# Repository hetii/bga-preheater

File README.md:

# BGA REWORK STATION
Advanced Open-Source BGA Preheater Controller with Web Interface, Multi-Zone Heating, and Thermal Profile Management.

---

## 📖 Overview

**BGA Rework Station** is a fully open-source project designed for controlling professional and DIY BGA/PCB preheating systems.

The controller supports multiple heating zones, thermocouple monitoring, fan control, and a modern web-based interface for managing the entire process directly from a browser.

The project is suitable for:
- BGA rework stations
- PCB preheaters
- SMT/reflow experiments
- Electronics repair workshops
- DIY thermal control systems

---

# ✨ Features

## 🔥 Multi-Zone Heater Control
- Control up to **5 independent heaters**
- Separate heating zones
- Real-time power management
- Suitable for IR heaters, ceramic heaters, hotplates, and custom heating systems

## 🌡️ Thermocouple Monitoring
- Support for **6 thermocouples** and ds18b20 sensors over 1 wire
- Real-time temperature acquisition
- Multi-point PCB temperature tracking
- Accurate thermal feedback for safe BGA processing

## 🌀 Fan Control
- PWM fan control support
- Automatic or manual cooling operation
- Active thermal stabilization

## 🌐 Web Interface
Built-in web application accessible from any browser.

Features include:
- Real-time temperature monitoring
- Heater control
- Fan management
- Profile editor
- System status monitoring
- Live thermal charts

## 💾 BGA Profile Management
- Save and load BGA heating profiles
- Custom temperature curves
- Repeatable rework processes
- Profile storage directly in the system

---

# 🛠️ Hardware Capabilities

| Feature | Specification |
|---|---|
| Heater Outputs | Up to 5 |
| Thermocouple Inputs | 6 |
| Fan Control | 2 x PWM Supported |
| Interface | Web Browser |
| Profile Storage | Supported |
| Open Source | Yes |

---

# 📂 Project Structure

```text
/
├── hardware
│   ├── grb
│   ├── img
│   ├── kicad
│   └── pdf
├── README.md
└── software
    ├── builder
    ├── builder.py
    ├── configs
    ├── html
    ├── include
    ├── requirements.txt
    └── src
```

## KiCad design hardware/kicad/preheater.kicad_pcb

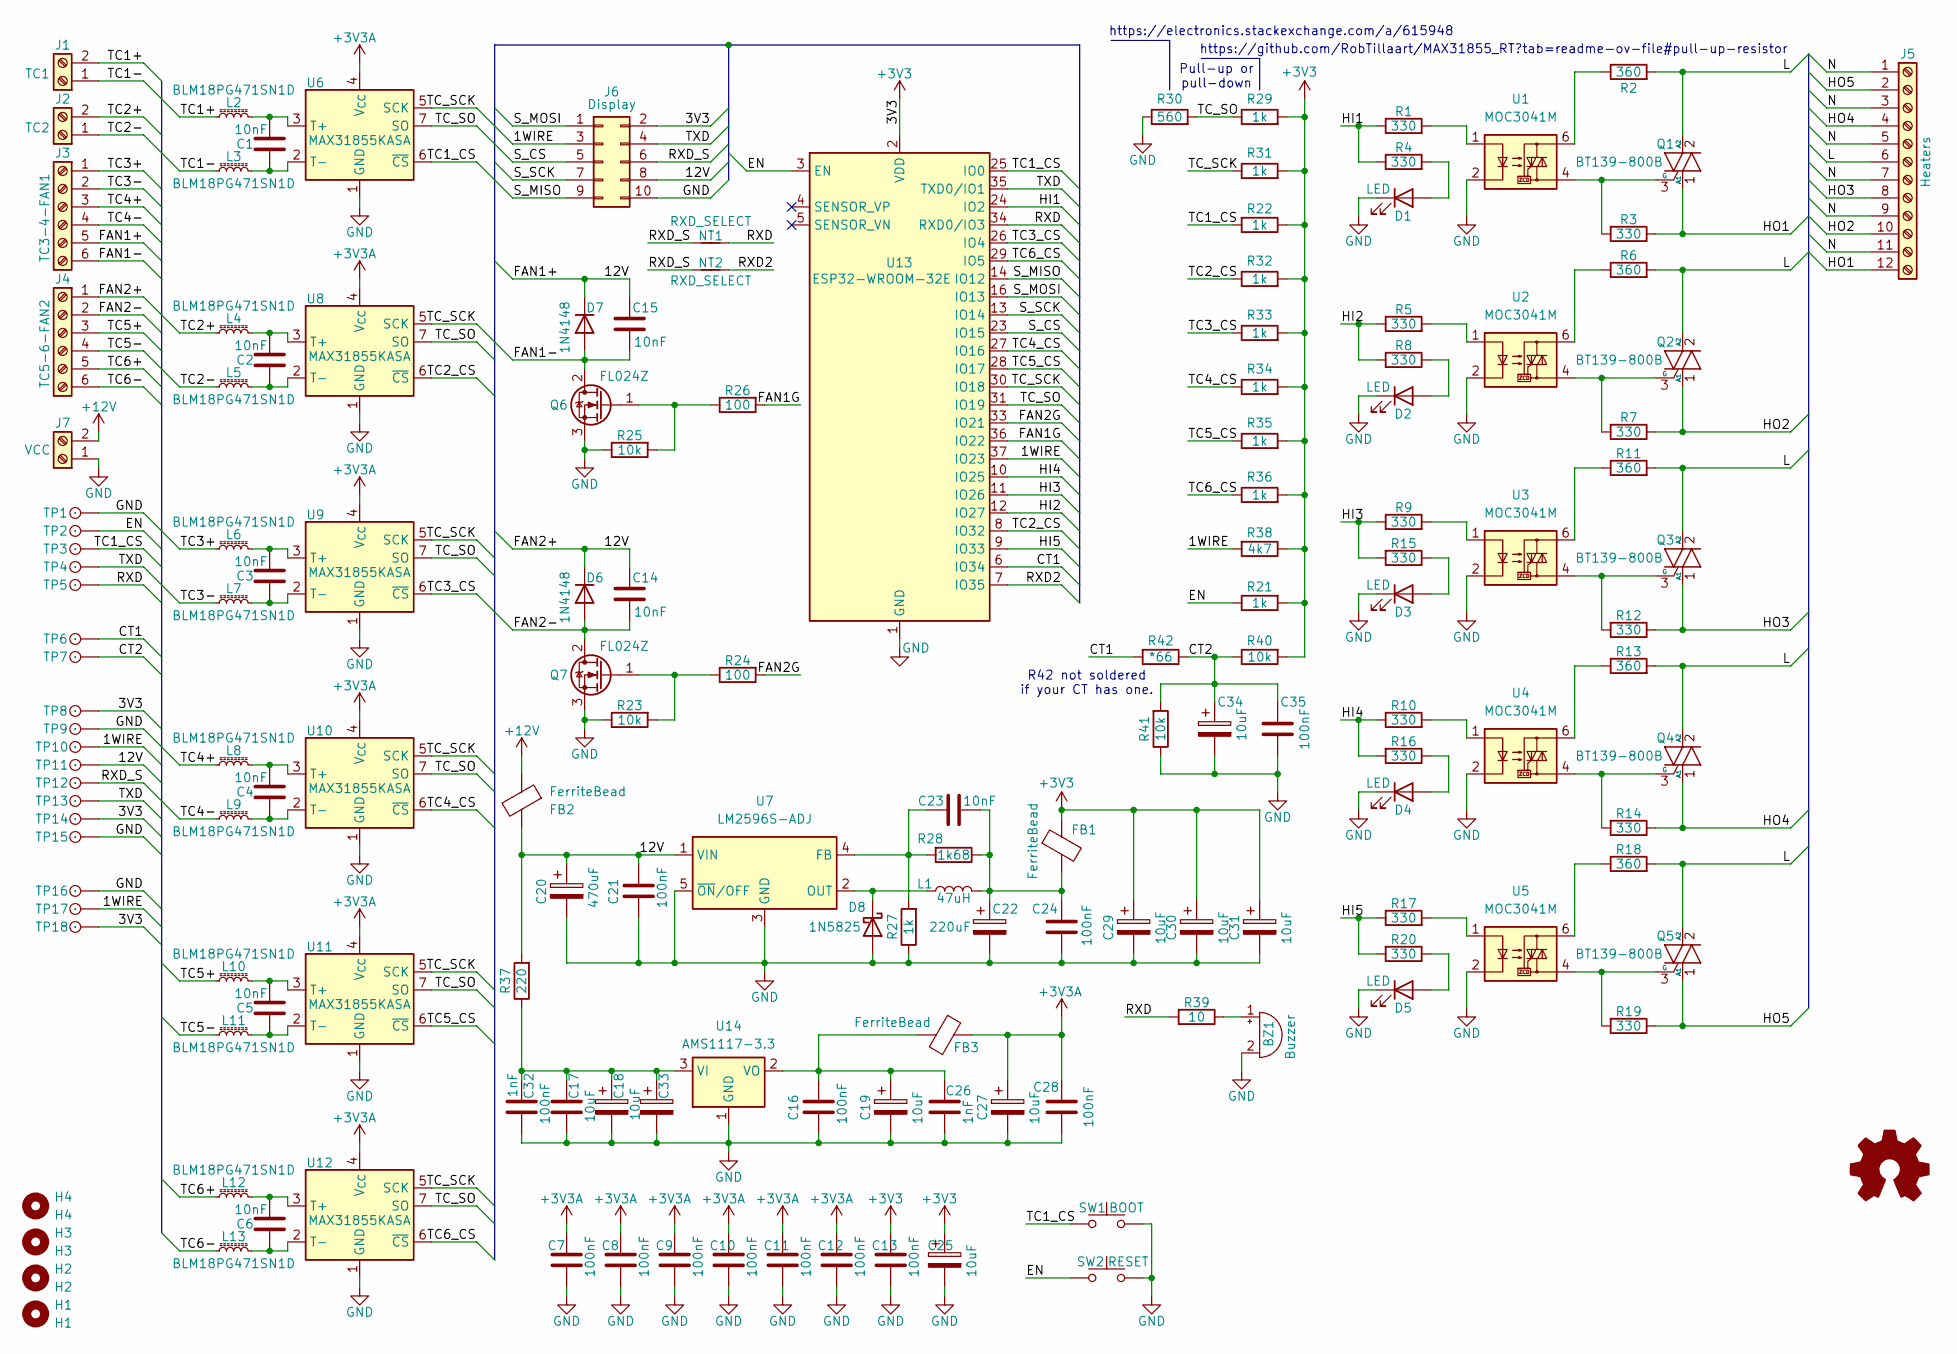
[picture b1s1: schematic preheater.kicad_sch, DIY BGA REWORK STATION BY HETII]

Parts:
BZ1: Buzzer; Buzzer_12x9.5RM7.6
C1, C2, C3, C4, C5, C6, C14, C15, C23: 10nF; C_1206_3216Metric_Pad1.33x1.80mm_HandSolder
C7, C8, C9, C10, C11, C12, C13, C16, C17, C21, C24, C28, C35: 100nF; C_1206_3216Metric_Pad1.33x1.80mm_HandSolder
C18, C19, C25, C27, C29, C30, C31, C33, C34: 10uF; C_1206_3216Metric_Pad1.33x1.80mm_HandSolder
C20: 470uF; CP_Radial_D8.0mm_P3.50mm
C22: 220uF; CP_Radial_D8.0mm_P3.50mm
C26, C32: 1nF; C_1206_3216Metric_Pad1.33x1.80mm_HandSolder
D1, D2, D3, D4, D5: LED; LED_1206_3216Metric_Pad1.42x1.75mm_HandSolder
D6, D7: 1N4148; D_MicroMELF_Handsoldering
D8: 1N5825; D_MicroMELF_Handsoldering
FB1, FB2: FerriteBead; L_Axial_L7.0mm_D3.3mm_P10.16mm_Horizontal_Fastron_MICC
FB3: FerriteBead; L_Axial_L7.0mm_D3.3mm_P2.54mm_Vertical_Fastron_MICC
H1: H1; MountingHole_3.2mm_M3_Pad_Via
H2: H2; MountingHole_3.2mm_M3_Pad_Via
H3: H3; MountingHole_3.2mm_M3_Pad_Via
H4: H4; MountingHole_3.2mm_M3_Pad_Via
J1: TC1; Altech_AK100_1x02_P5.00mm
J2: TC2; Altech_AK100_1x02_P5.00mm
J3: TC3-4-FAN1; Altech_AK100_1x06_P5.00mm
J4: TC5-6-FAN2; Altech_AK100_1x06_P5.00mm
J5: Heaters; Altech_AK300_1x12_P5.00mm_45-Degree
J6: Display; PinHeader_2x05_P2.54mm_Vertical
J7: VCC; Altech_AK100_1x02_P5.00mm
L1: 47uH; L_Bourns_SRR1260
L2, L3, L4, L5, L6, L8, L9, L10, L11, L12, L13: BLM18PG471SN1D; L_0603_1608Metric_Pad1.05x0.95mm_HandSolder
L7: BLM18PG471SN1D; R_0603_1608Metric_Pad0.98x0.95mm_HandSolder
NT1, NT2: RXD_SELECT; R_0201_0603Metric
Q1, Q2, Q3, Q4, Q5: BT139-800B; TO-220-3_Vertical
Q6, Q7: FL024Z; SOT-223-3_TabPin2
R1, R4, R5, R8, R9, R10, R15, R16, R17, R20: 330; R_1206_3216Metric_Pad1.30x1.75mm_HandSolder
R2, R6, R11, R13, R18: 360; R_1206_3216Metric_Pad1.30x1.75mm_HandSolder
R3, R7, R12, R14, R19: 330; R_Axial_DIN0204_L3.6mm_D1.6mm_P7.62mm_Horizontal
R21, R22, R27, R29, R31, R32, R33, R34, R35, R36: 1k; R_1206_3216Metric_Pad1.30x1.75mm_HandSolder
R23, R25, R40, R41: 10k; R_1206_3216Metric_Pad1.30x1.75mm_HandSolder
R24, R26: 100; R_1206_3216Metric_Pad1.30x1.75mm_HandSolder
R28: 1k68; R_1206_3216Metric_Pad1.30x1.75mm_HandSolder
R30: 560; R_1206_3216Metric_Pad1.30x1.75mm_HandSolder
R37: 220; R_1206_3216Metric_Pad1.30x1.75mm_HandSolder
R38: 4k7; R_1206_3216Metric_Pad1.30x1.75mm_HandSolder
R39: 10; R_1206_3216Metric_Pad1.30x1.75mm_HandSolder
R42: *66; R_1206_3216Metric_Pad1.30x1.75mm_HandSolder
SW1: BOOT; SW_SPST_PTS645Sx43SMTR92
SW2: RESET; SW_SPST_PTS645Sx43SMTR92
TP1, TP2, TP3, TP4, TP5, TP6, TP7, TP8, TP9, TP10, TP11, TP12, TP13, TP14, TP15, TP16, TP17, TP18: .; TestPoint_Pad_D1.5mm
U1, U2, U3, U4, U5: MOC3041M; DIP-6_W7.62mm_Socket_LongPads
U6, U8, U9, U10, U11, U12: MAX31855KASA; SOIC-8_3.9x4.9mm_P1.27mm
U7: LM2596S-ADJ; TO-263-5_TabPin3
U13: ESP32-WROOM-32E; ESP32-WROOM-32D
U14: AMS1117-3.3; SOT-223-3_TabPin2

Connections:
+3V3: C13.1, C25.1, C29.1, C30.1, C31.1, FB1.1, J6.2, R21.2, R22.1, R29.2, R31.2, R32.2, R33.2, R34.2, R35.2, R36.2, R38.1, R40.2, TP8.1, TP14.1, TP18.1, U13.2 (VDD)
+3V3A: C7.1, C8.1, C9.1, C10.1, C11.1, C12.1, C27.1, C28.2, FB3.1, U6.4 (V_{CC}), U8.4 (V_{CC}), U9.4 (V_{CC}), U10.4 (V_{CC}), U11.4 (V_{CC}), U12.4 (V_{CC})
+12V: FB2.1, J7.2
/1WIRE: J6.3, R38.2, TP10.1, TP17.1, U13.37 (IO23)
/12V: C14.1, C15.1, C20.1, C21.1, D6.1 (K), D7.1 (K), FB2.2, J3.5, J4.1, J6.8, R37.2, TP11.1, U7.1 (VIN)
/CT1: R42.2, TP6.1, U13.6 (IO34)
/CT2: C34.1, C35.1, R40.1, R41.2, R42.1, TP7.1
/EN: R21.1, SW2.1, TP2.1, U13.3 (EN)
/FAN1-: C15.2, D7.2 (A), J3.6, Q6.2 (D)
/FAN1G: R26.2, U13.36 (IO22)
/FAN2-: C14.2, D6.2 (A), J4.2, Q7.2 (D)
/FAN2G: R24.2, U13.33 (IO21)
/HI1: R1.1, R4.1, U13.24 (IO2)
/HI2: R5.1, R8.2, U13.12 (IO27)
/HI3: R9.1, R15.2, U13.11 (IO26)
/HI4: R10.1, R16.2, U13.10 (IO25)
/HI5: R17.1, R20.2, U13.9 (IO33)
/HO1: J5.12, Q1.1 (A1), R3.1
/HO2: J5.10, Q2.1 (A1), R7.1
/HO3: J5.8, Q3.1 (A1), R12.1
/HO4: J5.4, Q4.1 (A1), R14.1
/HO5: J5.2, Q5.1 (A1), R19.1
/L: J5.6, Q1.2 (A2), Q2.2 (A2), Q3.2 (A2), Q4.2 (A2), Q5.2 (A2), R2.2, R6.2, R11.2, R13.2, R18.2
/N: J5.1, J5.3, J5.5, J5.7, J5.9, J5.11
/RXD: NT1.2, R39.2, TP5.1, U13.34 (RXD0/IO3)
/RXD2: NT2.2, U13.7 (IO35)
/RXD_S: J6.6, NT1.1, NT2.1, TP12.1
/S_CS: J6.5, U13.23 (IO15)
/S_MISO: J6.9, U13.14 (IO12)
/S_MOSI: J6.1, U13.16 (IO13)
/S_SCK: J6.7, U13.13 (IO14)
/TC1+: J1.2, L2.2
/TC1-: J1.1, L3.2
/TC1_CS: R22.2, SW1.1, TP3.1, U6.6 (~CS), U13.25 (IO0)
/TC2+: J2.2, L4.2
/TC2-: J2.1, L5.2
/TC2_CS: R32.1, U8.6 (~CS), U13.8 (IO32)
/TC3+: J3.1, L6.2
/TC3-: J3.2, L7.2
/TC3_CS: R33.1, U9.6 (~CS), U13.26 (IO4)
/TC4+: J3.3, L8.2
/TC4-: J3.4, L9.2
/TC4_CS: R34.1, U10.6 (~CS), U13.27 (IO16)
/TC5+: J4.3, L10.2
/TC5-: J4.4, L11.2
/TC5_CS: R35.1, U11.6 (~CS), U13.28 (IO17)
/TC6+: J4.5, L12.2
/TC6-: J4.6, L13.2
/TC6_CS: R36.1, U12.6 (~CS), U13.29 (IO5)
/TC_SCK: R31.1, U6.5 (SCK), U8.5 (SCK), U9.5 (SCK), U10.5 (SCK), U11.5 (SCK), U12.5 (SCK), U13.30 (IO18)
/TC_SO: R29.1, R30.2, U6.7 (SO), U8.7 (SO), U9.7 (SO), U10.7 (SO), U11.7 (SO), U12.7 (SO), U13.31 (IO19)
/TXD: J6.4, TP4.1, TP13.1, U13.35 (TXD0/IO1)
GND: BZ1.2 (-), C7.2, C8.2, C9.2, C10.2, C11.2, C12.2, C13.2, C16.2, C17.2, C18.2, C19.2, C20.2, C21.2, C22.2, C24.2, C25.2, C26.2, C27.2, C28.1, C29.2, C30.2, C31.2, C32.2, C33.2, C34.2, C35.2, D1.1 (K), D2.1 (K), D3.1 (K), D4.1 (K), D5.1 (K), D8.2 (A), J6.10, J7.1, Q6.3 (S), Q7.3 (S), R23.1, R25.1, R27.1, R30.1, R41.1, SW1.2, SW2.2, TP1.1, TP9.1, TP15.1, TP16.1, U1.2, U2.2, U3.2, U4.2, U5.2, U6.1 (GND), U7.3 (GND), U7.5 (~ON/OFF), U8.1 (GND), U9.1 (GND), U10.1 (GND), U11.1 (GND), U12.1 (GND), U13.1 (GND), U13.15 (GND), U13.38 (GND), U13.39 (GND), U14.1 (GND)
unnamed: BZ1.1 (+), R39.1
unnamed: C22.1, C23.2, C24.1, FB1.2, L1.2, R28.1
unnamed: D1.2 (A), R4.2
unnamed: D2.2 (A), R8.1
unnamed: D3.2 (A), R15.1
unnamed: D4.2 (A), R16.1
unnamed: D5.2 (A), R20.1
unnamed: D8.1 (K), L1.1, U7.2 (OUT)
unnamed: Q1.3 (G), R3.2, U1.4
unnamed: Q2.3 (G), R7.2, U2.4
unnamed: Q3.3 (G), R12.2, U3.4
unnamed: Q4.3 (G), R14.2, U4.4
unnamed: Q5.3 (G), R19.2, U5.4
unnamed: Q6.1 (G), R25.2, R26.1
unnamed: Q7.1 (G), R23.2, R24.1
unnamed: R1.2, U1.1
unnamed: R2.1, U1.6
unnamed: R5.2, U2.1
unnamed: R6.1, U2.6
unnamed: R9.2, U3.1
unnamed: R10.2, U4.1
unnamed: R11.1, U3.6
unnamed: R13.1, U4.6
unnamed: R17.2, U5.1
unnamed: R18.1, U5.6
unnamed: C1.1, L2.1, U6.3 (T+)
unnamed: C1.2, L3.1, U6.2 (T-)
unnamed: C23.1, R27.2, R28.2, U7.4 (FB)
unnamed: C2.1, L4.1, U8.3 (T+)
unnamed: C2.2, L5.1, U8.2 (T-)
unnamed: C3.1, L6.1, U9.3 (T+)
unnamed: C3.2, L7.1, U9.2 (T-)
unnamed: C4.1, L8.1, U10.3 (T+)
unnamed: C4.2, L9.1, U10.2 (T-)
unnamed: C5.1, L10.1, U11.3 (T+)
unnamed: C5.2, L11.1, U11.2 (T-)
unnamed: C6.1, L12.1, U12.3 (T+)
unnamed: C6.2, L13.1, U12.2 (T-)
unnamed: C17.1, C18.1, C32.1, C33.1, R37.1, U14.3 (VI)
unnamed: C16.1, C19.1, C26.1, FB3.2, U14.2 (VO)

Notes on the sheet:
R42 not soldered if your CT has one.
Pull-up or pull-down
https://electronics.stackexchange.com/a/615948
https://github.com/RobTillaart/MAX31855_RT?tab=readme-ov-file#pull-up-resistor

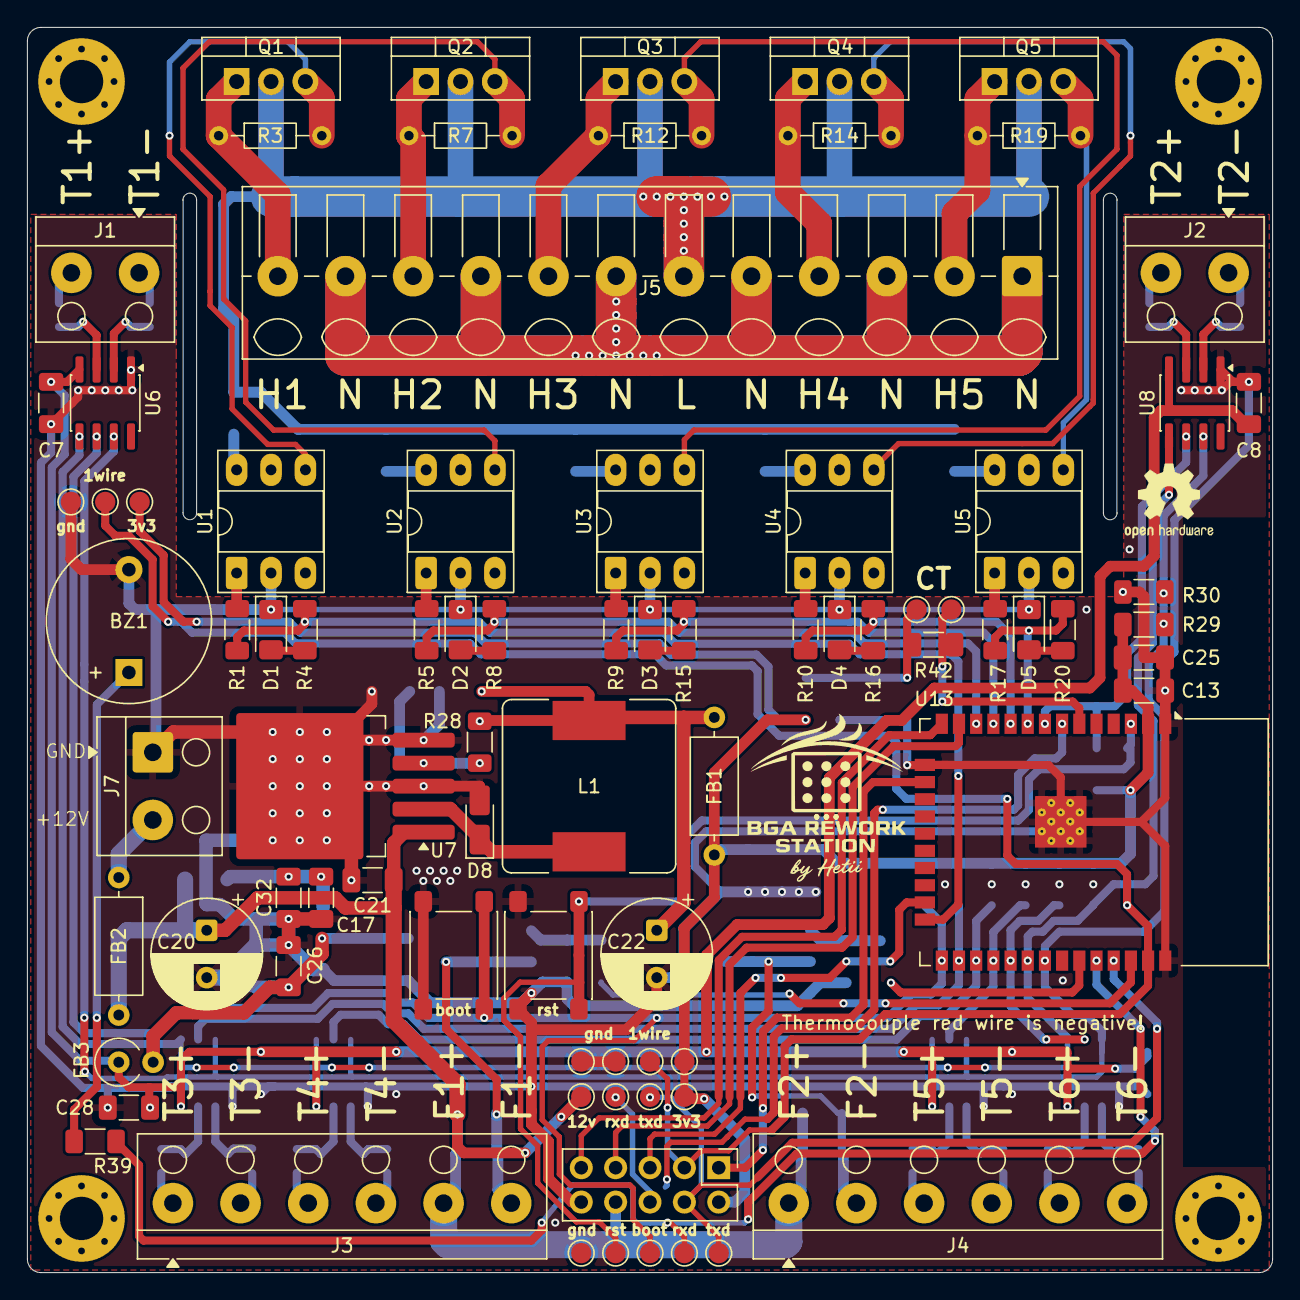
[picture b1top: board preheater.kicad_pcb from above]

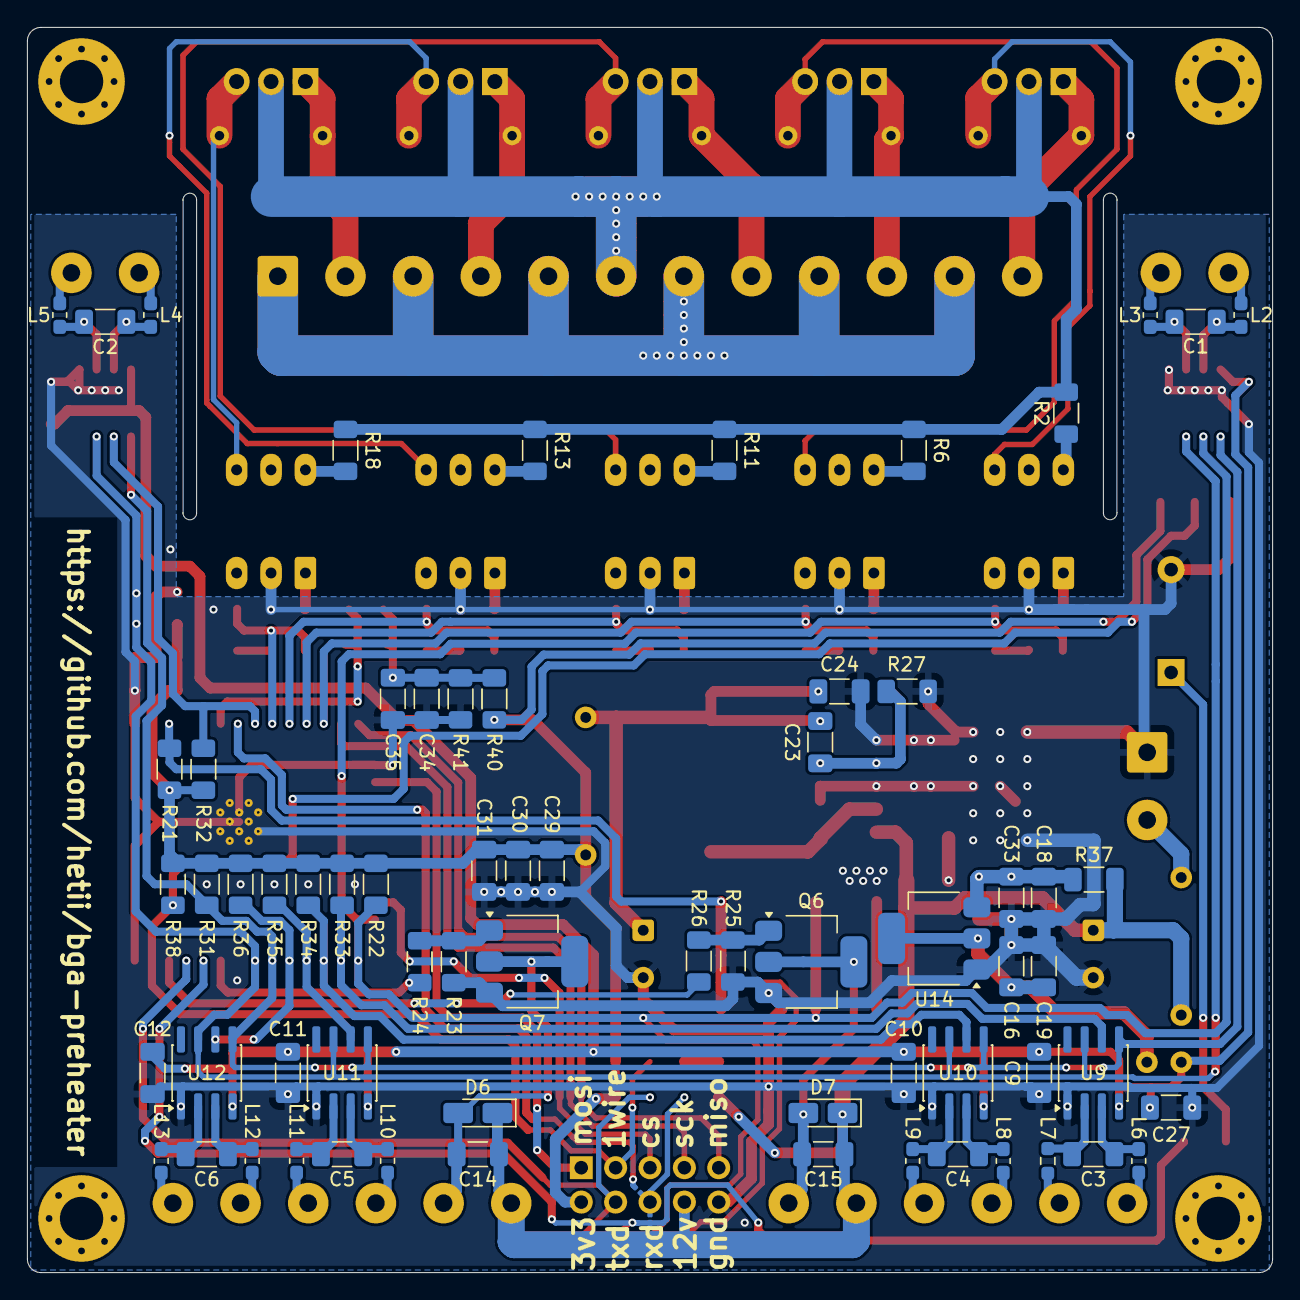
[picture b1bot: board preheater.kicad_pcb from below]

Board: 2 copper layers, 92.0 x 92.0 mm, 157 parts (69 on the bottom side), 93 nets.

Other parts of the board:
...: LOGO

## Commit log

2026-05-19 Initial commit.
